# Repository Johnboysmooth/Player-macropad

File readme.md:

# Player! V1.31

Player! is a five button macropad originally designed to accomodate changing music settings in Spotify without tabbing into the Spotify client. By default it is programmed to use dedicated media keys, which can be further optimised with global hotkeys using [Toastify](https://github.com/aleab/toastify) or [Volumey](https://apps.microsoft.com/store/detail/volumey/9MZCQ03MX0S3?hl=en-gb&gl=gb&rtc=1).

Using four cherry compatible switches, Player! provides dedicated keys for pausing/playing music -  returning to a previous song, and skipping to the next song. The fourth switch remains user programmable, binded to 'insert' by default to be used as dedicated Discord mute key. A rotary encoder allows for volume control, with a toggle function bound to its embedded switch to allow rotary control of rewinding and fast-forwarding music. Player! is entirely customisable, using [Vial](https://get.vial.today/) for rebinding keys.

V1.31 has made the Player! bigger to accommodate 4 mounting holes, which will be used to mount the PCB to a case. The otherwise empty space is covered in a tropical leaf pattern on the top copper layer; a number of changes have been made to improve the appearance and the fit/function of the base.

# Images
Assembled on Base:

Assembled PCB:

3D Model in KiCAD:

# Documentation

Build information can be found in this [document](/Player!_Info.pdf), covering topics such as the Bill of Materials and Flashing information.

## License
<br />Player! is licensed under a <a rel="license" href="http://creativecommons.org/licenses/by-nc/4.0/">Creative Commons Attribution-NonCommercial 4.0 International License </a>

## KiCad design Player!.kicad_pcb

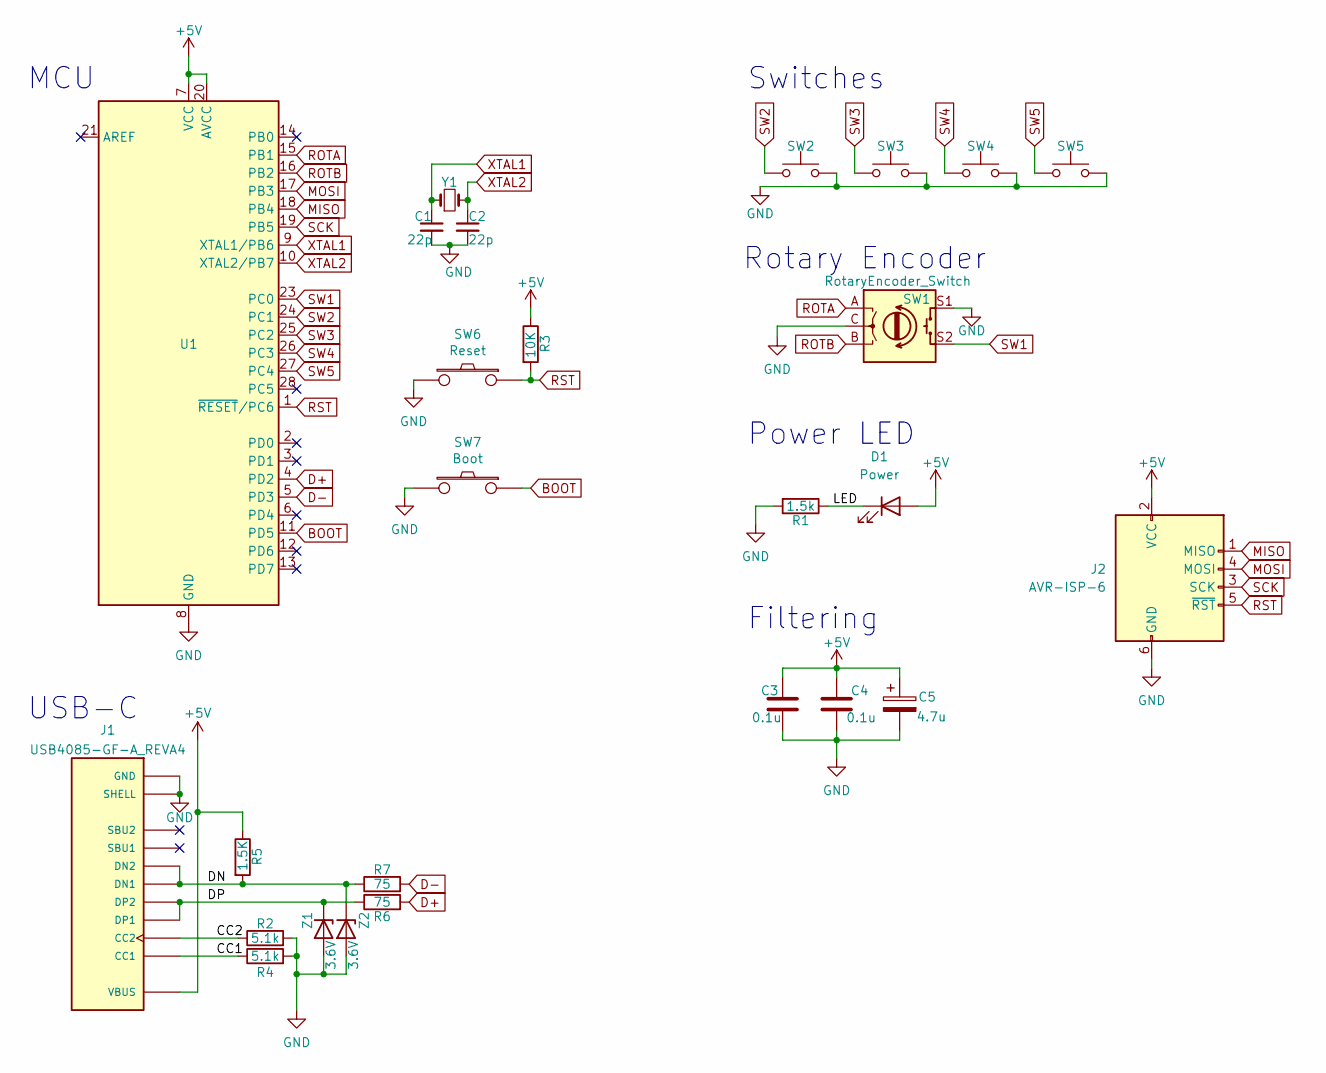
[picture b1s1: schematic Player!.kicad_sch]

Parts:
C1, C2: 22p; C_Disc_D3.0mm_W1.6mm_P2.50mm
C3, C4: 0.1u; C_Disc_D4.3mm_W1.9mm_P5.00mm
C5: 4.7u; CP_Radial_D4.0mm_P1.50mm
D1: Power; LED_D3.0mm
J1: USB4085-GF-A_REVA4; GCT_USB4085-GF-A_REVA4; PARTREV A4
J2: AVR-ISP-6; PinHeader_2x03_P2.54mm_Vertical
R1: 1.5k; R_Axial_DIN0204_L3.6mm_D1.6mm_P5.08mm_Horizontal
R2, R4: 5.1k; R_Axial_DIN0204_L3.6mm_D1.6mm_P5.08mm_Horizontal
R3: 10K; R_Axial_DIN0204_L3.6mm_D1.6mm_P5.08mm_Horizontal
R5: 1.5K; R_Axial_DIN0204_L3.6mm_D1.6mm_P5.08mm_Horizontal
R6, R7: 75; R_Axial_DIN0204_L3.6mm_D1.6mm_P5.08mm_Horizontal
SW1: RotaryEncoder_Switch; RotaryEncoder_Alps_EC12E-Switch_Vertical_H20mm
SW2, SW3, SW4, SW5: SW_Push; SW_Hotswap_Kailh_MX_1.00u
SW6: Reset; SW_PUSH_6mm
SW7: Boot; SW_PUSH_6mm
U1: ATmega328P-P; ATmega328p DIP-28
Y1: Crystal; Crystal_HC49-4H_Vertical
Z1, Z2: 3.6V; D_DO-35_SOD27_P5.08mm_Horizontal

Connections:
+5V: C3.1, C4.1, C5.1, D1.2 (A), J1.A4 (VBUS), J1.A9 (VBUS), J1.B4 (VBUS), J1.B9 (VBUS), J2.2 (VCC), R3.1, R5.1, U1.7 (VCC), U1.20 (AVCC)
/CC1: J1.A5 (CC1), R4.1
/CC2: J1.B5 (CC2), R2.1
/DN: J1.A7 (DN1), J1.B7 (DN2), R5.2, R7.1, Z2.1 (K)
/DP: J1.A6 (DP1), J1.B6 (DP2), R6.1, Z1.1 (K)
/LED: D1.1 (K), R1.1
BOOT: SW7.2, U1.11 (PD5)
D+: R6.2, U1.4 (PD2)
D-: R7.2, U1.5 (PD3)
GND: C1.2, C2.2, C3.2, C4.2, C5.2, J1.A1 (GND), J1.A12 (GND), J1.B1 (GND), J1.B12 (GND), J1.P1 (SHELL), J1.P2 (SHELL), J1.P3 (SHELL), J1.P4 (SHELL), J2.6 (GND), R1.2, R2.2, R4.2, SW1.C, SW1.S1, SW2.2, SW3.2, SW4.2, SW5.2, SW6.1, SW7.1, U1.8 (GND), U1.22 (GND), Z1.2 (A), Z2.2 (A)
MISO: J2.1 (MISO), U1.18 (PB4)
MOSI: J2.4 (MOSI), U1.17 (PB3)
ROTA: SW1.A, U1.15 (PB1)
ROTB: SW1.B, U1.16 (PB2)
RST: J2.5 (~RST), R3.2, SW6.2, U1.1 (~RESET/PC6)
SCK: J2.3 (SCK), U1.19 (PB5)
SW1: SW1.S2, U1.23 (PC0)
SW2: SW2.1, U1.24 (PC1)
SW3: SW3.1, U1.25 (PC2)
SW4: SW4.1, U1.26 (PC3)
SW5: SW5.1, U1.27 (PC4)
XTAL1: C1.1, U1.9 (XTAL1/PB6), Y1.1
XTAL2: C2.1, U1.10 (XTAL2/PB7), Y1.2

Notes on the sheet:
USB-C
Switches
Rotary Encoder
Power LED
MCU
Filtering

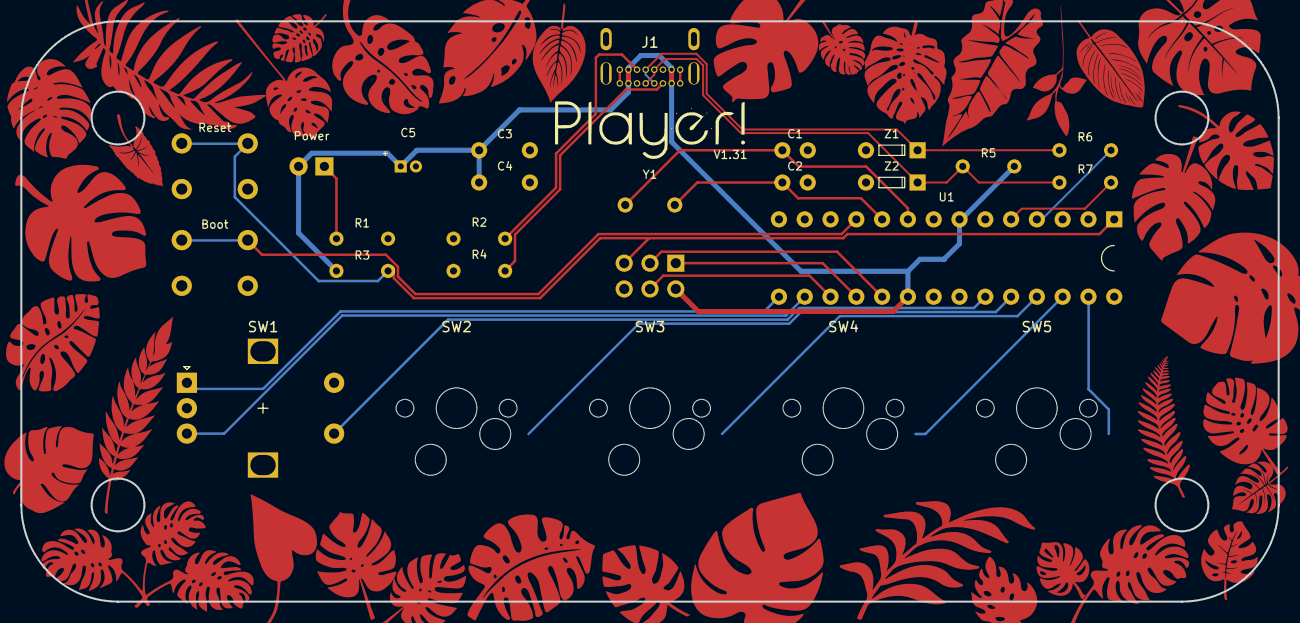
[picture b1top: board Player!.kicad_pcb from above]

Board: 2 copper layers, 123.8 x 57.1 mm, 26 parts (0 on the bottom side), 23 nets.

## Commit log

2022-08-26 PCB & Libraries
2022-08-26 Case Model
2022-08-26 Updated readme with images
2022-08-26 Upload firmware hex files
2023-06-18 Updated to V1.31
    V1.31 makes the bigger to accommodate 4 mounting holes, adds a decorative tropical pattern to the top copper plane in the otherwise blank space; numerous small changes made to improve the overall app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
2023-06-18 PCB changes
    Minor changes to correct D+ & D- tracks connecting
2023-07-01 Final PCB changes for v1.31
2023-07-01 Readme tweaks, updated .hex file
2023-07-10 Delete Player!-backups directory
    This should have never been included lmao
2023-08-20 Updated silkscreen
2023-08-20 Added base
    Added 3d printable base as well as 3d printable standoffs.
2023-08-20 Documentation cleanup
    Cleaning up the readme by creating a separate document for build information
2023-08-20 Fixing links in Info PDF
